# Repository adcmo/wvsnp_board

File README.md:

# wvsnp_board

What is it?

This is the official board schematic, files, BOM and manufacturer files for the WVSNP Reduced board.

This is the Schematic and PCB layout (including gerber files) for the WVSNP Reduced Carrier Board 
and supporting components.

License and Copyright

This is the official repository of WVSNP Project. All code, SW and Hardware contributed here is 
subject to NDA and agreements you have with the WVSNP Project and ASU.

Quick Start Guide:

NOTE- The following work was done on Ubuntu version 14. Everything should be viewable on Windows or Mac however the 3D viewer will not properly work because of the different directory structures. They will have to be manually changed in KiCAD. 

Questions or concerns: Kevin Virgen kvirgen@gmail.com

1- Download version 4.0.4 of Kicad at http://kicad-pcb.org/download/
Other versions do not work properly with the 3D viewer.

2- Download Wings 3D for 3D model creation at http://www.wings3d.com/

3- Download FreeCAd for 3D model creation at http://www.freecadweb.org/

4- Get a copy of the repository: - Using Command Prompt (Git Bash) git clone 
   //https://github.com/adcmo/wvsnp_board.git
   - Using the GitHub page While logged in to GitHub, there are URLs available 
    in the sidebar: HTTPS clone URL - Using GitHub's GUI to clone repo.

5- Once repo is copied open Kicad - Choose File -> Open Project or CTRL+o - 
   Select "WVSNP_Reduced_board_hand.kicad_pcb.pro" file

   This will open the entire project with all the files necessary to see and 
   edit the schematic and PCB layout. 

3D - To view the board in 3D drag the contents of the folder "add_these_to_packages3d"  and "custom3D" into the "/usr/share/kicad/modules/packages3d" folder.
   This may require root privileges. Then click View -> 3D viewer. If it is still not working 
   you may need to change the permission on the new files because kiCAD seems picky on them.
   Another error may be directory location. If a 3D image of a footprint is not showing up in "3D View" 
   make sure it's pointing to the correct directory by navigation to the footprint's 3D settings menu.  
	- An in Dept tutorial on how to make 3D models is located here
	https://sethkoberg.wordpress.com/2014/03/30/tutorial-custom-3d-models-for-kicad-3d-viewer/
   
6- Making Changes to schematic - Double click on "Board-To-Board.sch" inside the "schematics" folder. 
   This will open the schematic - Make any necessary changes (add/removing 
   components, adding wires, etc) - If any components were added, ensure values 
   are properly filled (see any kicad tutorials) - Once happy with your changes, 
   save it and click the "NET" icon in the tool bar and follow prompts. This step 
   ensures components are populated in PCB side of things. - Run the CvPCB tool 
   to assign footprints for your components and save changes
   - A current video of the 3D model can be seen at :
	https://www.dropbox.com/s/u4em6s6bgvm3ido/WVSNP_Reduced_board.mp4?dl=0

7- Making changes to PCB file - Double click on "WVSNP_Reduced_Board_hand.kicad_pcb" 
   - If components were added, click on "NET" on tool bar and click "Read Current 
     Netlist" This should add all the components you added to the schematic assuming 
     you have footprints available. If you don't have a footprint, look up tutorials 
     on how to create footprints. NOTE: If you assigned an existing footprint and it 
     doesn't populate, check to see if there are warnings after reading the netlist.

   - Once you finished routing all traces and placing all components, save it and run 
     "design rules check" (lady bug on tool bar).
     NOTE: Ensure that the place you are planning to have the boards manufactured 
     support your design rules. Set the design rules before making any changes.

   - Fix any issues that the checker points out. 
   - Save your changes and click "Plot" on toolbar (looks like a printer). Here you'll 
     generate your Gerbers. If you are unsure on what you'd like to add on the Gerbers, 
     look up toturials for generating Gerber files in Kicad. 

BOM

The Revision_BOM is part of the Repo (Excel file). 

Commiting Changes

Follow the same procedures as you would for any files. If using Git Bash, check which 
files have been changed with "git status" or if using GUI, see which files are showing 
in the change window.

Submitting Files for Fabrication

The zipped folder "Fab Files" have everything you need to send it for fabrication. 
Just submit the compressed folder and the shops know what to do with it. If you made 
changes, you'll need to generate new Gerber files and submit those. If you missed any 
important Gerbers (edge cuts for example) the shops will generally ask you for them

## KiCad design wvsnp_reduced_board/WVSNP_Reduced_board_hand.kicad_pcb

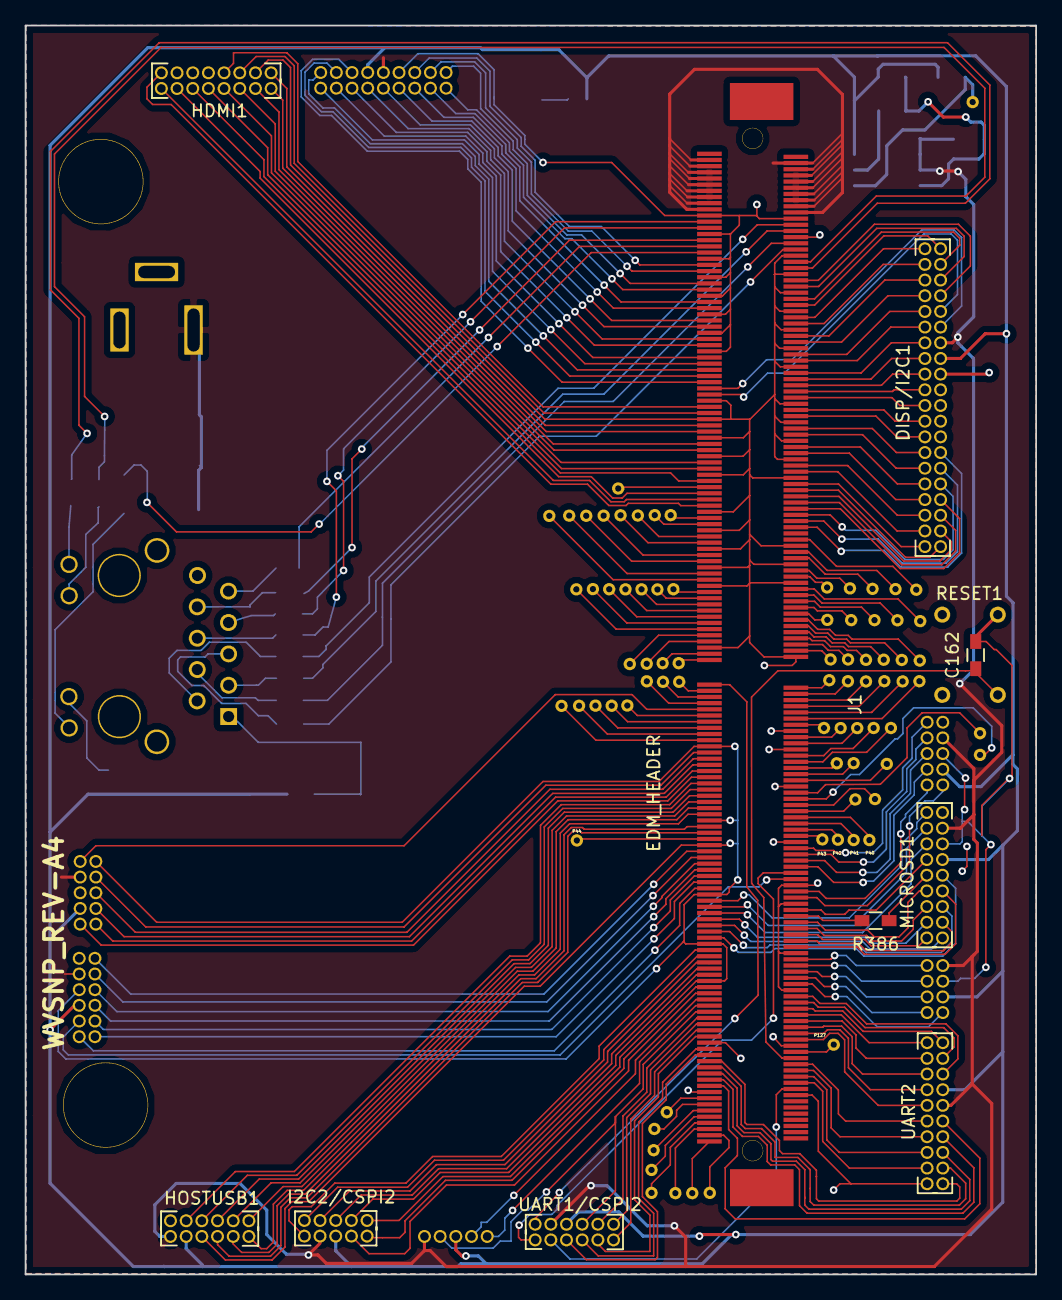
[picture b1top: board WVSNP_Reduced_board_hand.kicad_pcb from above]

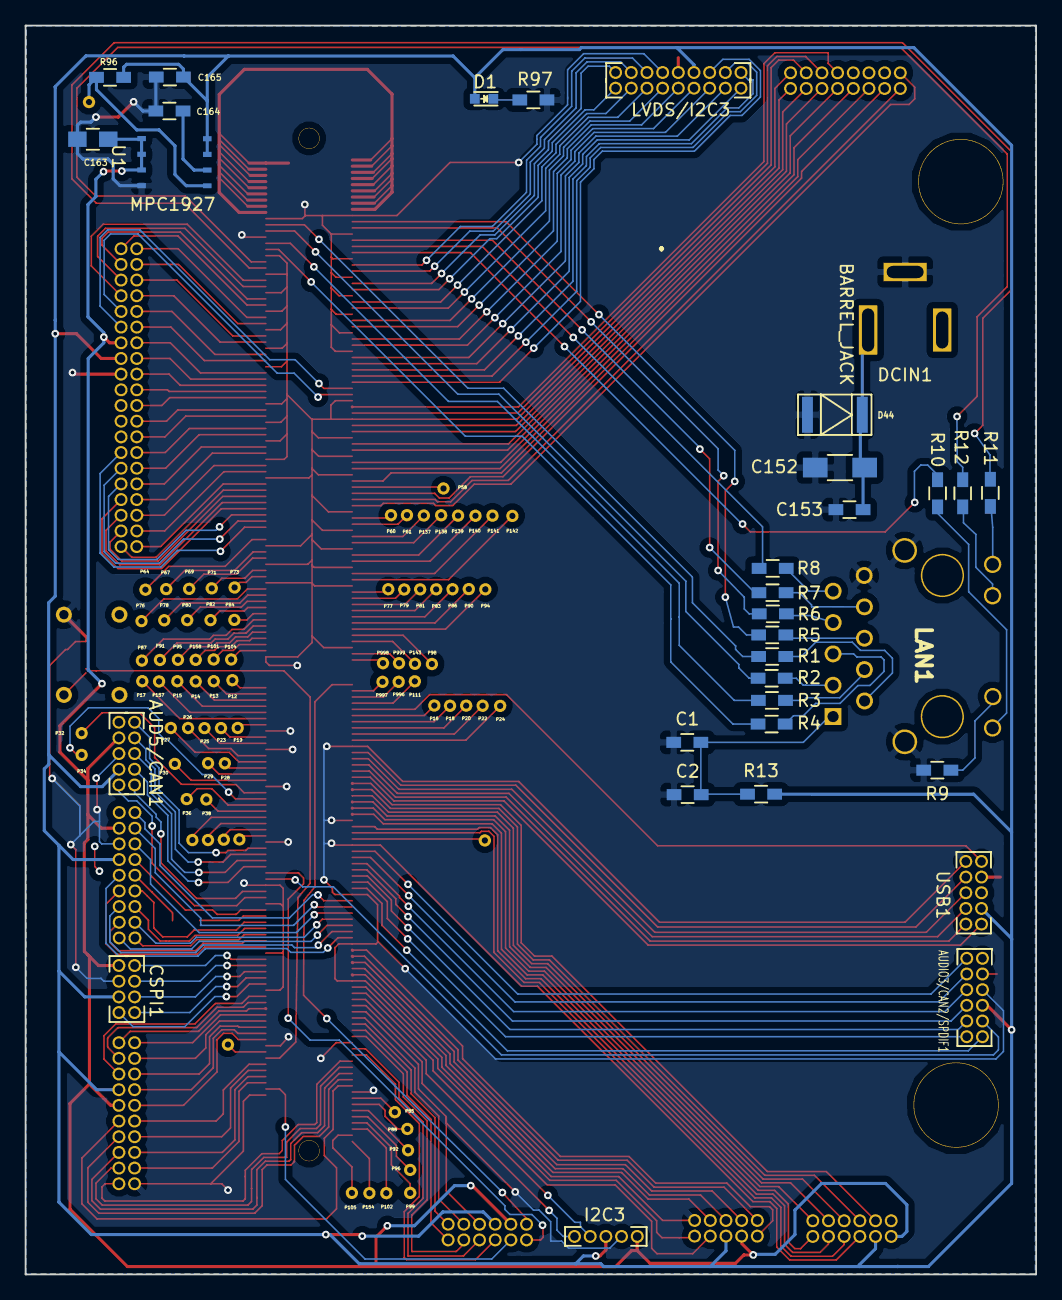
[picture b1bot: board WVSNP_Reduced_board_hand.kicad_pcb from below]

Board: 4 copper layers, 81.9 x 101.2 mm, 120 parts (103 on the bottom side), 247 nets.

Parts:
AUD5/CAN1: CONN_10; Pin_Header_Straight_2x5_127
AUDIO3/CAN2/SPDIF1: CONN_12; Pin_Header_Straight_2x6_127
C1: 1000P; R_0603_HandSoldering
C2: 0.1u; R_0603_HandSoldering
C152: 22u; C_1206_HandSoldering
C153: 4.7u; R_0603_HandSoldering
C162: .22U; R_0603_HandSoldering
C163: 4.7u; C_0805_HandSoldering
C164: 1n; R_0603_HandSoldering
C165: 11u; R_0603_HandSoldering
CSPI1: CONN_8; Pin_Header_Straight_2x4_127
D1: LED; LED-0603
D44: ZENER; SM0603
DCIN1: BARREL_JACK; Wand_DC_Jack
DISP/I2C1: CONN_40; Pin_Header_Straight_2x20_127
HDMI1: CONN_16; Pin_Header_Straight_2x8_127
HOSTUSB1: CONN_12; Pin_Header_Straight_2x6_127
I2C2/CSPI2: CONN_10; Pin_Header_Straight_2x5_127
I2C3: CONN_5; Pin_Header_Straight_1x5_127
J1: EDM_HEADER; EDM_HEADER_MXM3.0
LAN1: RT7-174AAM1A; WAND_RJ45_TRANSFO
LVDS/I2C3: CONN_18; Pin_Header_Straight_2x8_127
MICROSD1: CONN_18; Pin_Header_Straight_2x8_127
P12, P13, P14, P15, P16, P17, P18, P19, P20, P22, P23, P24, P25, P26, P27, P28, P29, P30, P32, P34, P36, P38, P40, P41, P42, P43, P44, P58, P60, P61, P64, P67, P69, P71, P73, P76, P77, P78, P79, P80, P81, P82, P83, P84, P85, P86, P87, P88, P90, P91, P92, P94, P95, P96, P98, P99, P101, P102, P104, P105, P111, P127, P137, P138, P139, P140, P141, P142, P143, P154, P157, P158, P996, P997, P998, P999: TST; TEST_POINT
R1, R2, R3, R4, R5, R6, R7, R8, R9, R11, R386: 0; R_0603_HandSoldering
R10, R12, R97: 330; R_0603_HandSoldering
R13: 10; R_0603_HandSoldering
R96: 6.04k; R_0603_HandSoldering
RESET1: SW_PUSH; Wand_Push_button
U1: MPC1927; Wand_AME_8816
UART1/CSPI2: CONN_12; Pin_Header_Straight_2x6_127
UART2: CONN_20; Pin_Header_Straight_2x10_127
USB1: CONN_10; Pin_Header_Straight_2x5_127

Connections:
+3.3V: AUD5/CAN1.9, AUDIO3/CAN2/SPDIF1.9, C165.1, CSPI1.3, D1.2, DISP/I2C1.33, HOSTUSB1.8, I2C2/CSPI2.8, I2C3.3, LVDS/I2C3.13, MICROSD1.15, R13.2, R96.2, U1.7, U1.8, UART1/CSPI2.4, UART2.17, USB1.7
+5V: AUD5/CAN1.7, AUDIO3/CAN2/SPDIF1.11, C152.1, C153.1, C163.1, CSPI1.1, D44.2, DCIN1.1, DISP/I2C1.34, HOSTUSB1.7, I2C2/CSPI2.7, I2C3.5, J1.E1_2, J1.E1_3, J1.E1_4, J1.E1_5, J1.E1_6, J1.E1_7, J1.E1_8, J1.E1_9, J1.E2_2, J1.E2_3, J1.E2_4, J1.E2_5, J1.E2_6, J1.E2_7, J1.E2_8, J1.E2_9, J1.E110, J1.E210, LVDS/I2C3.14, MICROSD1.17, U1.1, U1.2, U1.3, UART1/CSPI2.5, UART2.16, USB1.9
/EXCDA_nPREST: J1.107, P81.1
/GND_DRAIN1: J1.147, P20.1
/HDMI1_CAD: J1.69, P58.1
/MNF7: J1.267, P85.1
/MNF8: J1.269, P88.1
/MNF9: J1.271, P92.1
/MNF10: J1.273, P96.1
/MNF11: J1.275, P99.1
/MNF12: J1.277, P102.1
/MNF13_WATCHDOG: J1.279, P105.1
/PCIEA_CLKN: J1.87, P138.1
/PCIEA_CLKP: J1.85, P137.1
/PCIEA_RXN: J1.99, P142.1
/PCIEA_RXP: J1.97, P141.1
/PCIEA_TXN: J1.93, P140.1
/PCIEA_TXP: J1.91, P139.1
/PCIEB_CLKN: J1.81, P61.1
/PCIEB_CLKP: J1.79, P60.1
/PCIEB_RXN: J1.111, P86.1
/PCIEB_RXP: J1.109, P83.1
/PCIEB_TXN: J1.105, P79.1
/PCIEB_TXP: J1.103, P77.1
/PCIE_CLK_OEA: J1.113, P90.1
/PCIE_CLK_OEB: J1.115, P94.1
/PCIE_nRST: J1.119, P143.1
/PCIE_nWAKE: J1.117, P98.1
/PWR_BTN: J1.252, P127.1
/RSVD1: J1.114, P91.1
/R_NANDF_A1: J1.144, P17.1
/R_NANDF_A2: J1.142, P157.1
/R_NANDF_A3: J1.140, P15.1
/R_NANDF_A4: J1.138, P14.1
/R_NANDF_A5: J1.136, P13.1
/R_NANDF_A6: J1.134, P12.1
/R_NANDF_A7: J1.122, P104.1
/R_NANDF_A8: J1.120, P101.1
/R_NANDF_A9: J1.118, P158.1
/R_NANDF_A10: J1.116, P95.1
/R_NANDF_ALE: J1.108, P82.1
/R_NANDF_CLE: J1.106, P80.1
/R_NANDF_CS0: J1.86, P64.1
/R_NANDF_CS1: J1.90, P67.1
/R_NANDF_CS2: J1.92, P69.1
/R_NANDF_CS3: J1.96, P71.1
/R_NANDF_CS4: J1.98, P73.1
/R_NANDF_D0: J1.182, P43.1
/R_NANDF_D1: J1.180, P42.1
/R_NANDF_D2: J1.178, P41.1
/R_NANDF_D3: J1.176, P40.1
/R_NANDF_D4: J1.174, P38.1
/R_NANDF_D5: J1.172, P36.1
/R_NANDF_D6: J1.170, P34.1
/R_NANDF_D7: J1.168, P32.1
/R_NANDF_D8: J1.164, P30.1
/R_NANDF_D9: J1.162, P29.1
/R_NANDF_D10: J1.160, P28.1
/R_NANDF_D11: J1.158, P27.1
/R_NANDF_D12: J1.156, P26.1
/R_NANDF_D13: J1.152, P25.1
/R_NANDF_D14: J1.150, P23.1
/R_NANDF_D15: J1.146, P19.1
/R_NANDF_RB0: J1.102, P76.1
/R_NANDF_RE: J1.112, P87.1
/R_NANDF_WE: J1.110, P84.1
/R_NANDF_WP: J1.104, P78.1
/SATA1_RXN: J1.125, P998.1
/SATA1_RXP: J1.123, P999.1
/SATA1_TXN: J1.137, P996.1
/SATA1_TXP: J1.135, P997.1
/StdB1_SSRXN: J1.145, P18.1
/StdB1_SSRXP: J1.143, P16.1
/StdB1_SSTXN: J1.151, P24.1
/StdB1_SSTXP: J1.149, P22.1
/USB_H1_VBUS: J1.183, P44.1
/USB_HUB_RESET_B: J1.139, P111.1
/VCC_RTC: J1.281, P154.1
AUD3_RXD: AUDIO3/CAN2/SPDIF1.1, J1.187
AUD3_TXC: AUDIO3/CAN2/SPDIF1.4, J1.193
AUD3_TXD: AUDIO3/CAN2/SPDIF1.3, J1.191
AUD3_TXFS: AUDIO3/CAN2/SPDIF1.2, J1.189
AUD5_RXD: AUD5/CAN1.5, J1.186
AUD5_TXC: AUD5/CAN1.2, J1.192
AUD5_TXD: AUD5/CAN1.3, J1.190
AUD5_TXFS: AUD5/CAN1.4, J1.188
AUDIO_CLK: AUDIO3/CAN2/SPDIF1.5, J1.195
AUX_5V_EN: J1.257, UART2.12
CAN1n: AUD5/CAN1.10, J1.202
CAN1p: AUD5/CAN1.1, J1.200
CAN2n: AUDIO3/CAN2/SPDIF1.7, J1.199
CAN2p: AUDIO3/CAN2/SPDIF1.6, J1.197
CSPI1_CS0: CSPI1.5, J1.228
CSPI1_CS1: CSPI1.4, J1.230
CSPI1_MISO: CSPI1.7, J1.224
CSPI1_MOSI: CSPI1.8, J1.222
CSPI1_SCLK: CSPI1.6, J1.226
CSPI2_CS0: I2C2/CSPI2.3, J1.225
CSPI2_CS1: I2C2/CSPI2.2, J1.227
CSPI2_MISO: I2C2/CSPI2.5, J1.221
CSPI2_MOSI: I2C2/CSPI2.6, J1.219
CSPI2_SCLK: I2C2/CSPI2.4, J1.223
DDC_SCL: HDMI1.9, J1.73
DDC_SDA: HDMI1.8, J1.75
DISP0_BKLEN: DISP/I2C1.27, J1.82
DISP0_CLK: DISP/I2C1.21, J1.70
DISP0_CNTRST: DISP/I2C1.24, J1.76
DISP0_DAT0: DISP/I2C1.37, J1.2
DISP0_DAT1: DISP/I2C1.38, J1.4
DISP0_DAT2: DISP/I2C1.39, J1.8
DISP0_DAT3: DISP/I2C1.40, J1.10
DISP0_DAT4: DISP/I2C1.1, J1.14
DISP0_DAT5: DISP/I2C1.2, J1.16
DISP0_DAT6: DISP/I2C1.3, J1.20
DISP0_DAT7: DISP/I2C1.4, J1.22
DISP0_DAT8: DISP/I2C1.5, J1.26
DISP0_DAT9: DISP/I2C1.6, J1.28
DISP0_DAT10: DISP/I2C1.7, J1.32
DISP0_DAT11: DISP/I2C1.8, J1.34
DISP0_DAT12: DISP/I2C1.9, J1.36
DISP0_DAT13: DISP/I2C1.10, J1.38
DISP0_DAT14: DISP/I2C1.11, J1.40
DISP0_DAT15: DISP/I2C1.12, J1.44
DISP0_DAT16: DISP/I2C1.13, J1.46
DISP0_DAT17: DISP/I2C1.14, J1.50
DISP0_DAT18: DISP/I2C1.15, J1.52
DISP0_DAT19: DISP/I2C1.16, J1.56
DISP0_DAT20: DISP/I2C1.17, J1.58
DISP0_DAT21: DISP/I2C1.18, J1.62
DISP0_DAT22: DISP/I2C1.19, J1.64
DISP0_DAT23: DISP/I2C1.20, J1.68
DISP0_DRDY: DISP/I2C1.25, J1.78
DISP0_HSYNC: DISP/I2C1.22, J1.72
DISP0_VDDEN: DISP/I2C1.26, J1.80
DISP0_VSYNC: DISP/I2C1.23, J1.74
ETHER1_D0N: J1.E4_3, R2.1
ETHER1_D0P: J1.E4_2, R1.1
ETHER1_D1N: J1.E4_6, R4.1
ETHER1_D1P: J1.E4_5, R3.1
ETHER1_D2N: J1.E3_3, R6.1
ETHER1_D2P: J1.E3_2, R5.1
ETHER1_D3N: J1.E3_6, R8.1
ETHER1_D3P: J1.E3_5, R7.1
GND: AUD5/CAN1.8, AUDIO3/CAN2/SPDIF1.10, C1.1, C2.1, C152.2, C153.2, C162.2, C163.2, C164.2, C165.2, CSPI1.2, D44.1, DCIN1.3, DISP/I2C1.32, HDMI1.2, HOSTUSB1.9, I2C2/CSPI2.1, I2C3.4, J1.1, J1.6, J1.7, J1.12, J1.13, J1.18, J1.19, J1.24, J1.25, J1.30, J1.41, J1.42, J1.47, J1.48, J1.53, J1.54, J1.59, J1.60, J1.65, J1.66, J1.77, J1.83, J1.88, J1.89, J1.94, J1.95, J1.100, J1.101, J1.121, J1.124, J1.148, J1.153, J1.154, J1.166, J1.177, J1.184, J1.185, J1.198, J1.201, J1.204, J1.217, J1.220, J1.229, J1.232, J1.239, J1.249, J1.250, J1.265, J1.266, J1.E3_1, J1.E3_4, J1.E3_8, J1.E4_1, J1.E4_4, J1.E4_7, J1.E410, LAN1.10, LAN1.H1, LAN1.H2, LVDS/I2C3.15, MICROSD1.16, R9.2, R97.2, RESET1.1, U1.4, UART1/CSPI2.3, UART2.10, USB1.1
GND_DRAIN2: HOSTUSB1.2, J1.171
GPIO1_24: J1.262, UART2.9
GPIO3_8: J1.261, UART2.14
GPIO3_11: J1.256, UART2.6
GPIO3_12: J1.255, UART2.11
GPIO3_26: J1.259, UART2.13
GPIO3_27: J1.258, UART2.7
GPIO6_1: J1.133, UART1/CSPI2.6
GPIO6_31: J1.260, UART2.8
GPIO7_8: J1.264, UART1/CSPI2.8
GPIO_1_CLK0: J1.194, UART1/CSPI2.7
GPIO_19: J1.263, UART2.15
HDMI1_CEC: HDMI1.10, J1.71
HDMI1_HPD: HDMI1.11, J1.67
HDMI_CLKM: HDMI1.3, J1.45
HDMI_CLKP: HDMI1.4, J1.43
HDMI_D0M: HDMI1.16, J1.51
HDMI_D0P: HDMI1.1, J1.49
HDMI_D1M: HDMI1.14, J1.57
HDMI_D1P: HDMI1.15, J1.55
HDMI_D2M: HDMI1.12, J1.63
HDMI_D2P: HDMI1.13, J1.61
I2C1_SCL: DISP/I2C1.36, J1.39
I2C1_SDA: DISP/I2C1.35, J1.37
I2C2_SCL: I2C2/CSPI2.10, J1.231
I2C2_SDA: I2C2/CSPI2.9, J1.233
I2C3_SCL: I2C3.2, J1.235
I2C3_SDA: I2C3.1, J1.237
LED1_ACT: J1.E3_7, R10.2
LED1_nLINK100: J1.E4_8, R12.2
LED1_nLINK1000: J1.E4_9, R11.2
LVDS0_BLT_CTRL: J1.27, LVDS/I2C3.8
LVDS0_CLK_N: J1.21, LVDS/I2C3.6
LVDS0_CLK_P: J1.23, LVDS/I2C3.7
LVDS0_EN: J1.29, LVDS/I2C3.9
LVDS0_TX0_N: J1.E3_9, LVDS/I2C3.16
LVDS0_TX0_P: J1.E310, LVDS/I2C3.17
LVDS0_TX1_N: J1.3, LVDS/I2C3.18
LVDS0_TX1_P: J1.5, LVDS/I2C3.1
LVDS0_TX2_N: J1.9, LVDS/I2C3.2
LVDS0_TX2_P: J1.11, LVDS/I2C3.3
LVDS0_TX3_N: J1.15, LVDS/I2C3.4
LVDS0_TX3_P: J1.17, LVDS/I2C3.5
LVDS0_VDDEN: J1.31, LVDS/I2C3.10
unnamed: D1.1, R97.1
unnamed: C164.1, R96.1, U1.5, U1.6
unnamed: LAN1.5, R4.2
unnamed: LAN1.4, R3.2
unnamed: LAN1.3, R2.2
unnamed: LAN1.2, R1.2
unnamed: LAN1.9, R8.2
unnamed: LAN1.8, R7.2
unnamed: LAN1.7, R6.2
unnamed: LAN1.6, R5.2
unnamed: LAN1.L1, R9.1
unnamed: LAN1.L4, R12.1
unnamed: LAN1.L3, R11.1
unnamed: LAN1.L2, R10.1
unnamed: C1.2, C2.2, LAN1.1, R13.1
S3: J1.251, UART1/CSPI2.10
S5: J1.253, UART1/CSPI2.9
SD1_CD: J1.203, MICROSD1.1
SD1_CLK: J1.206, MICROSD1.4
SD1_CMD: J1.205, MICROSD1.2
SD1_DATA0: J1.212, MICROSD1.7
SD1_DATA1: J1.209, MICROSD1.8
SD1_DATA2: J1.214, MICROSD1.9
SD1_DATA3: J1.211, MICROSD1.10
SD1_DATA4: J1.216, MICROSD1.11
SD1_DATA5: J1.213, MICROSD1.12
SD1_DATA6: J1.218, MICROSD1.13
SD1_DATA7: J1.215, MICROSD1.14
SD1_LED: J1.208, MICROSD1.5, R386.1, R386.2
SD1_PWREN: J1.210, MICROSD1.6
SD1_WP: J1.207, MICROSD1.3
SPDIF_OUT: AUDIO3/CAN2/SPDIF1.8, J1.196
StdB2_SSRXN: HOSTUSB1.3, J1.169
StdB2_SSRXP: HOSTUSB1.4, J1.167
StdB2_SSTXN: HOSTUSB1.12, J1.175
StdB2_SSTXP: HOSTUSB1.1, J1.173
UART1_CTS: J1.241, UART1/CSPI2.2
UART1_RTS: J1.247, UART1/CSPI2.11
UART1_RXD: J1.245, UART1/CSPI2.12
UART1_TXD: J1.243, UART1/CSPI2.1
UART2_CTS: J1.234, UART2.18
UART2_DCD: J1.242, J1.248, UART2.2, UART2.5
UART2_DSR: J1.244, UART2.3
UART2_DTR: J1.246, UART2.4
UART2_RTS: J1.240, UART2.1
UART2_RXD: J1.238, UART2.20
UART2_TXD: J1.236, UART2.19
USB_H1_OC: HOSTUSB1.5, J1.165
USB_HOST_DN: HOSTUSB1.11, J1.179
USB_HOST_DP: HOSTUSB1.10, J1.181
USB_OTG_DN: J1.159, USB1.4
USB_OTG_DP: J1.157, USB1.3
USB_OTG_ID: J1.155, USB1.2
USB_OTG_OC: J1.141, USB1.10
USB_OTG_PWR_EN: J1.163, USB1.6
USB_OTG_VBUS: J1.161, USB1.5
eDP0_HPD: J1.35, LVDS/I2C3.12
eDP0_SELF_TEST: J1.33, LVDS/I2C3.11
nRESET_BTN: C162.1, J1.254, RESET1.2

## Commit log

2015-11-12 initial push
2015-11-13 ignore ".DS_Store" flash drive files.
2015-12-03 clean up
2015-12-03 start over
2015-12-03 readme
2015-12-04 almost
2015-12-04 final
2015-12-04 add readme
2015-12-04 fixed link in readme
2015-12-04 fixed readme again
